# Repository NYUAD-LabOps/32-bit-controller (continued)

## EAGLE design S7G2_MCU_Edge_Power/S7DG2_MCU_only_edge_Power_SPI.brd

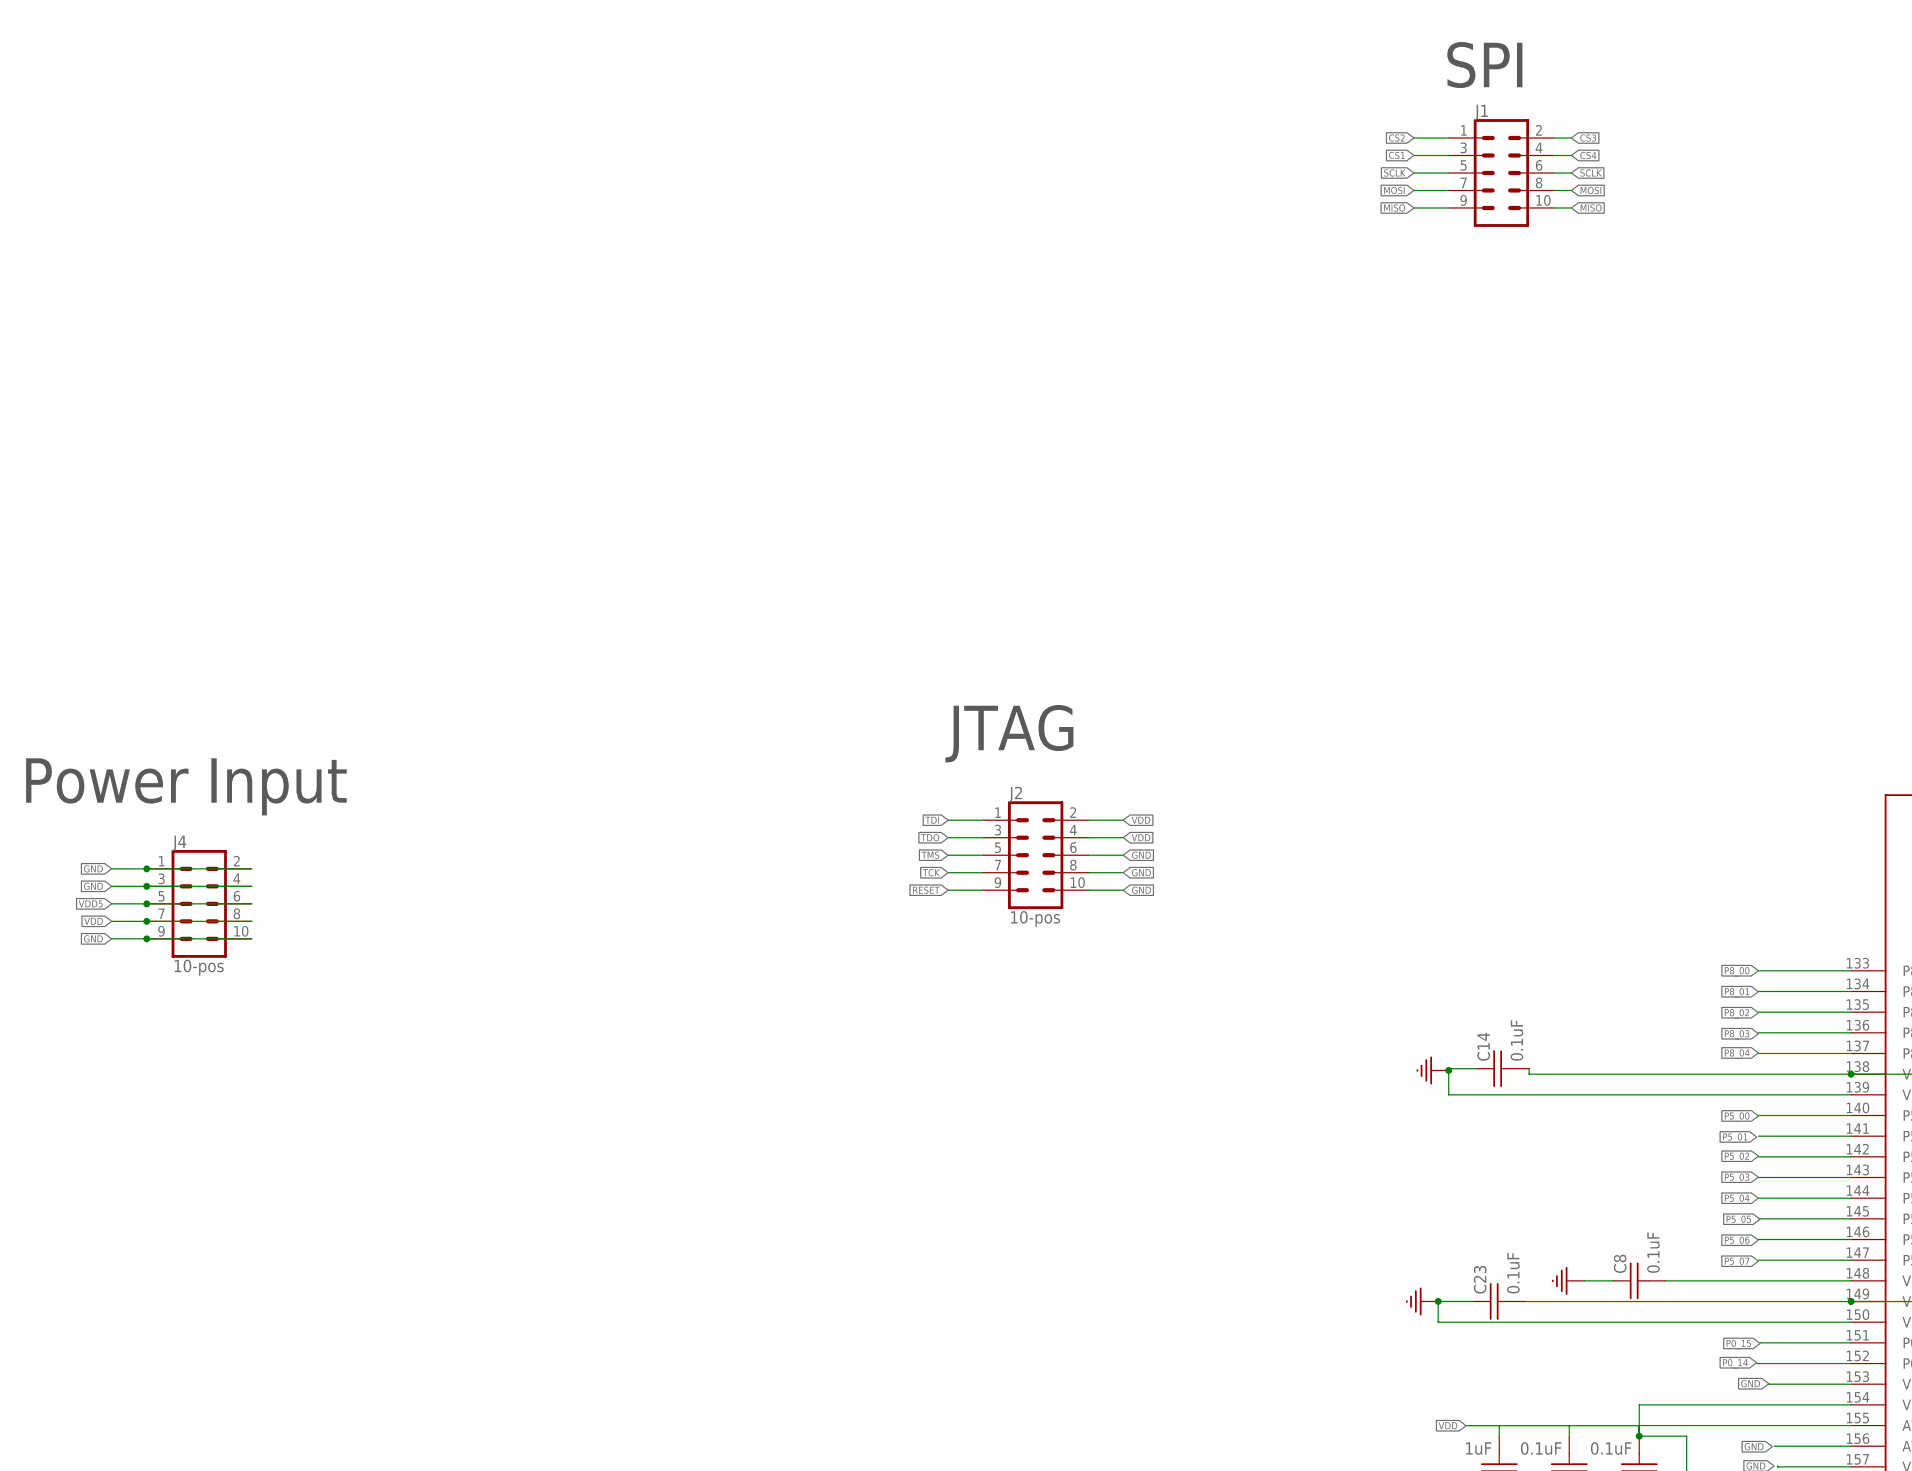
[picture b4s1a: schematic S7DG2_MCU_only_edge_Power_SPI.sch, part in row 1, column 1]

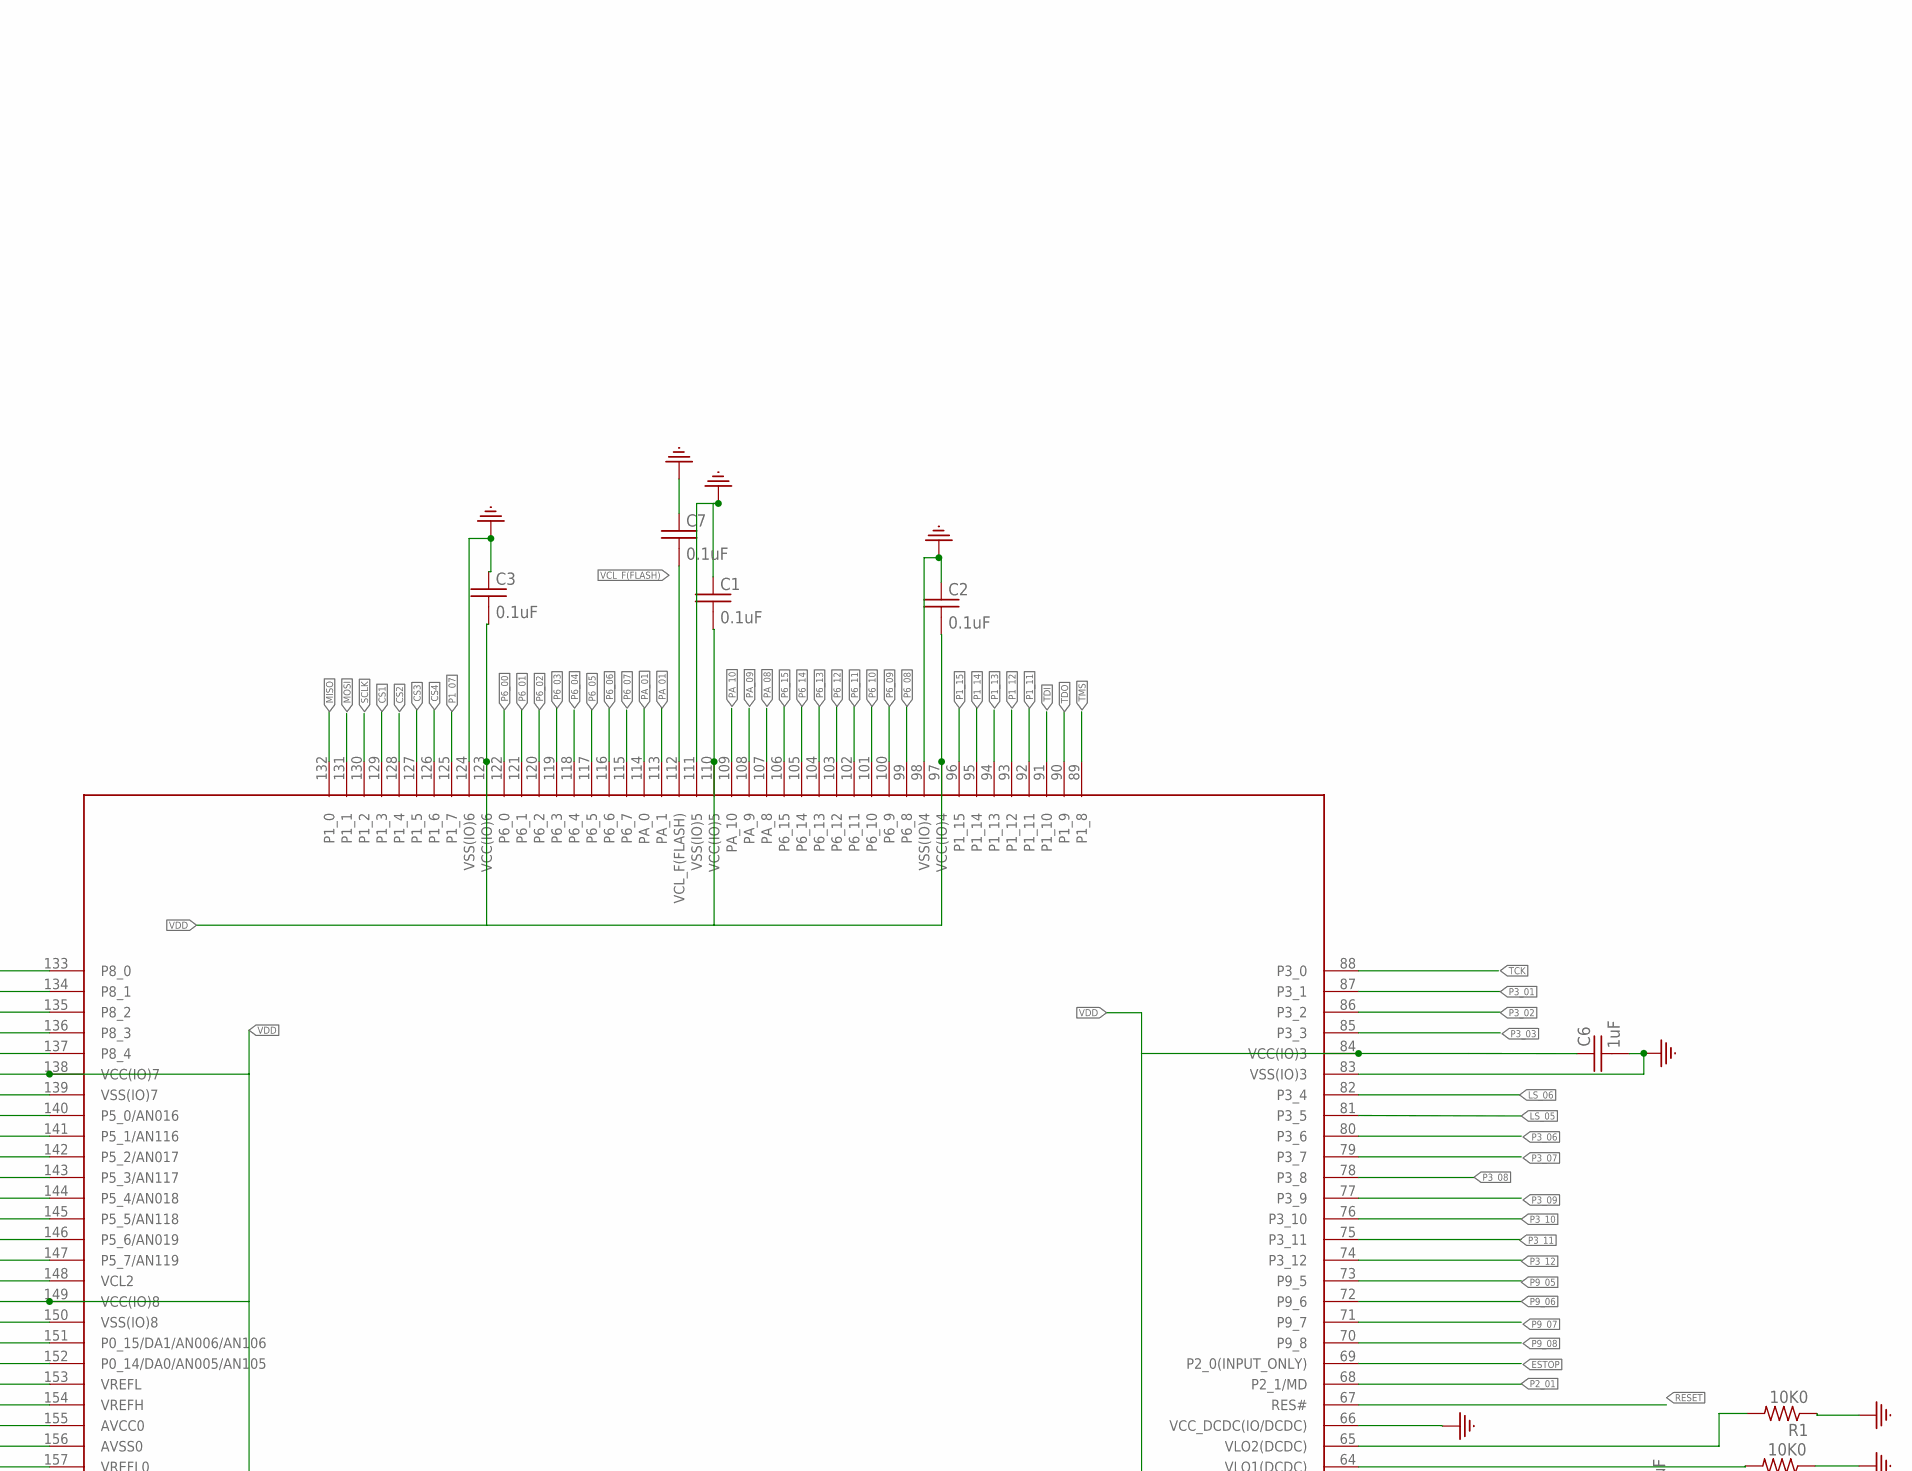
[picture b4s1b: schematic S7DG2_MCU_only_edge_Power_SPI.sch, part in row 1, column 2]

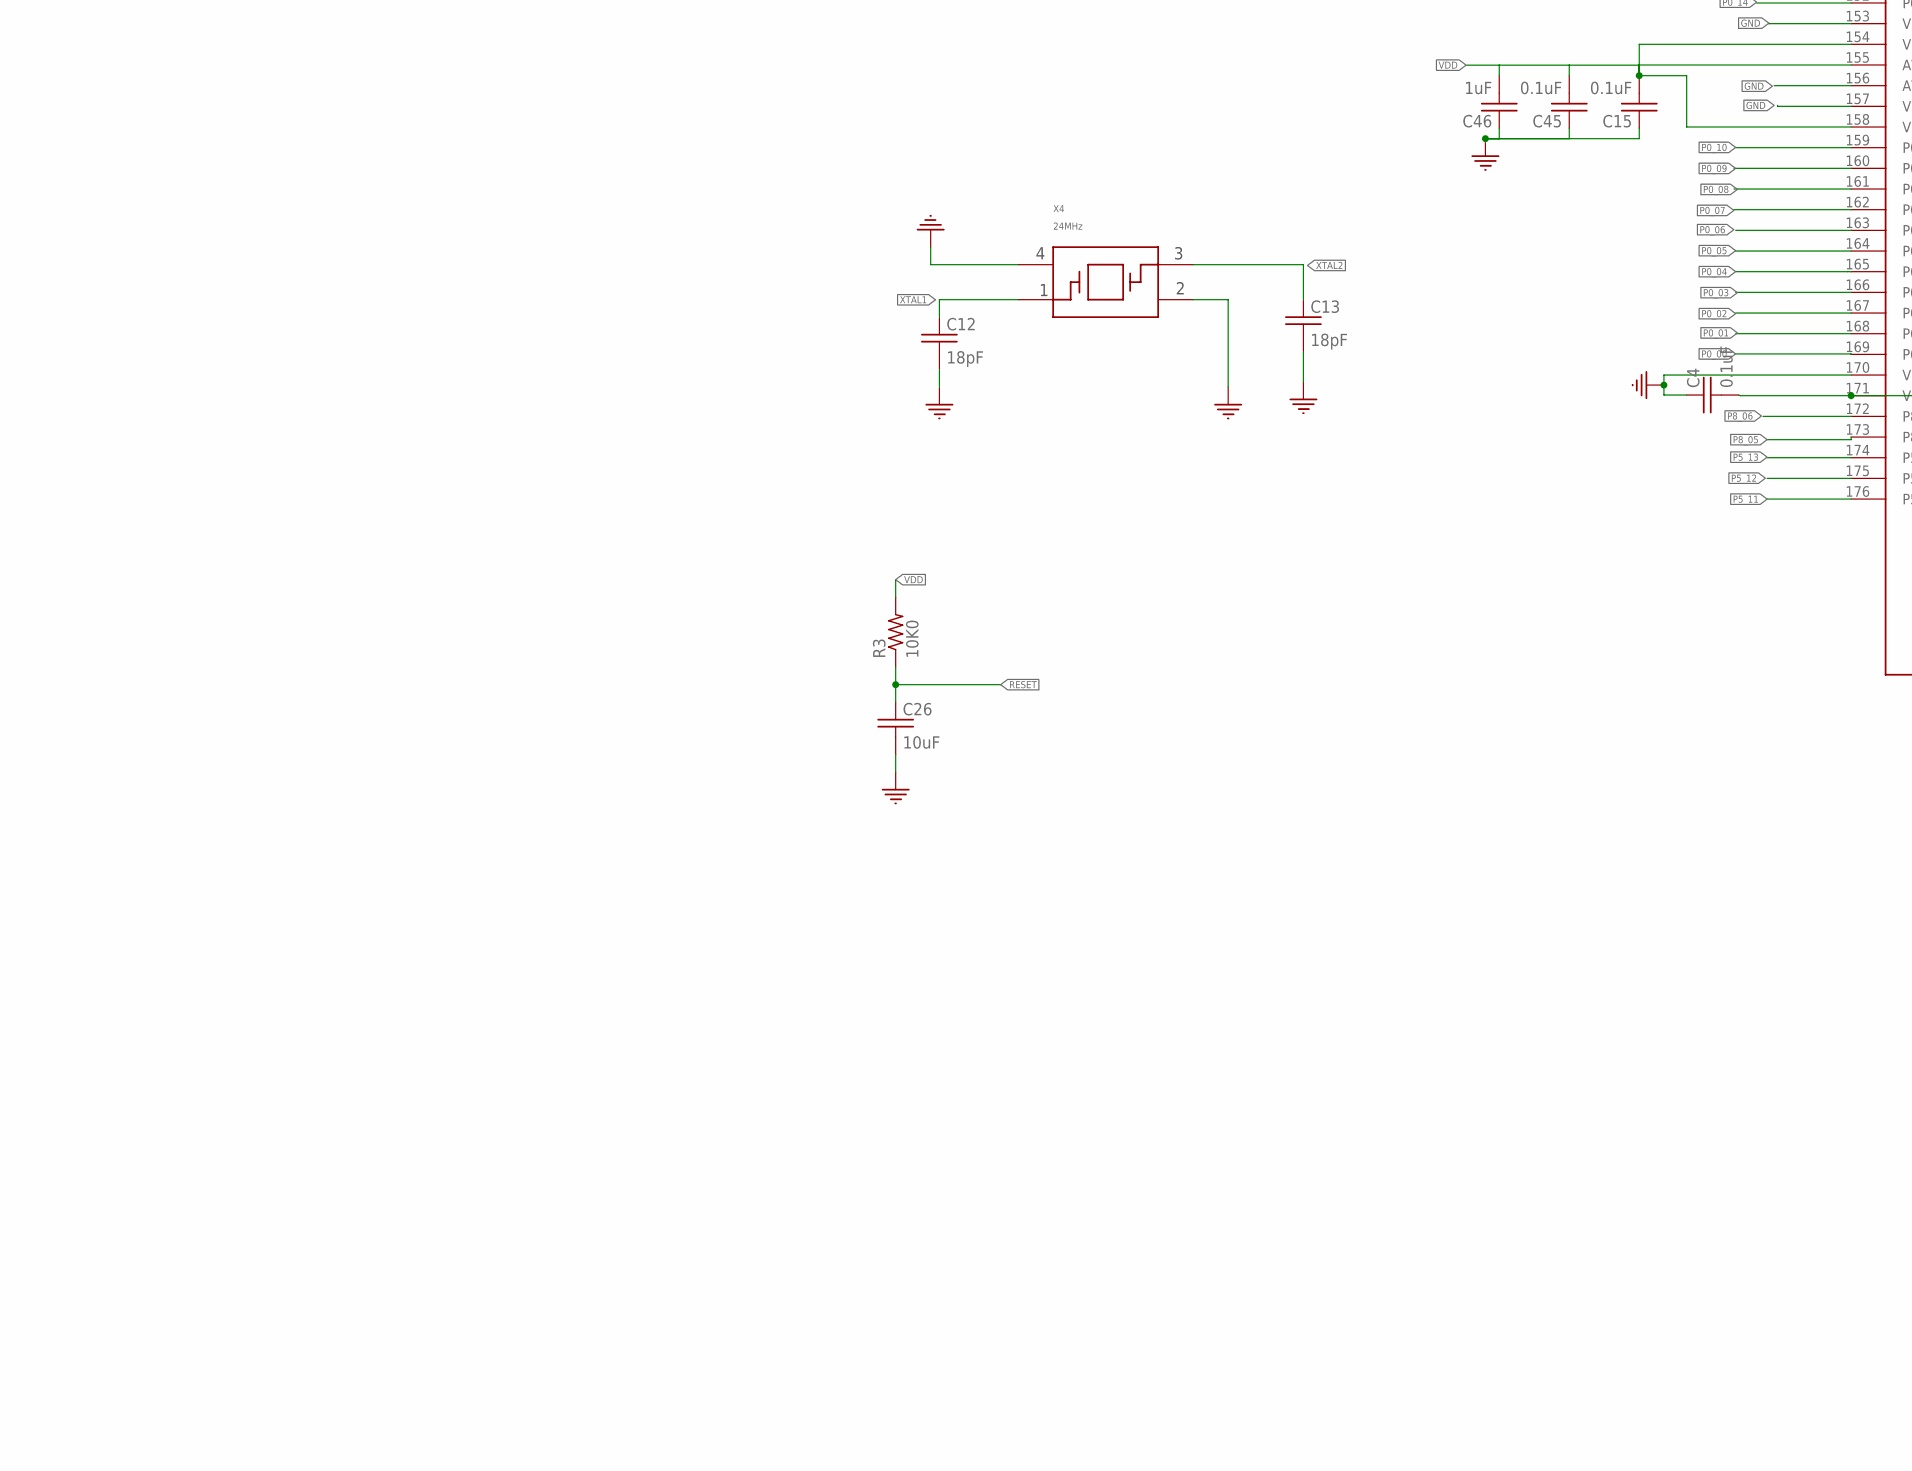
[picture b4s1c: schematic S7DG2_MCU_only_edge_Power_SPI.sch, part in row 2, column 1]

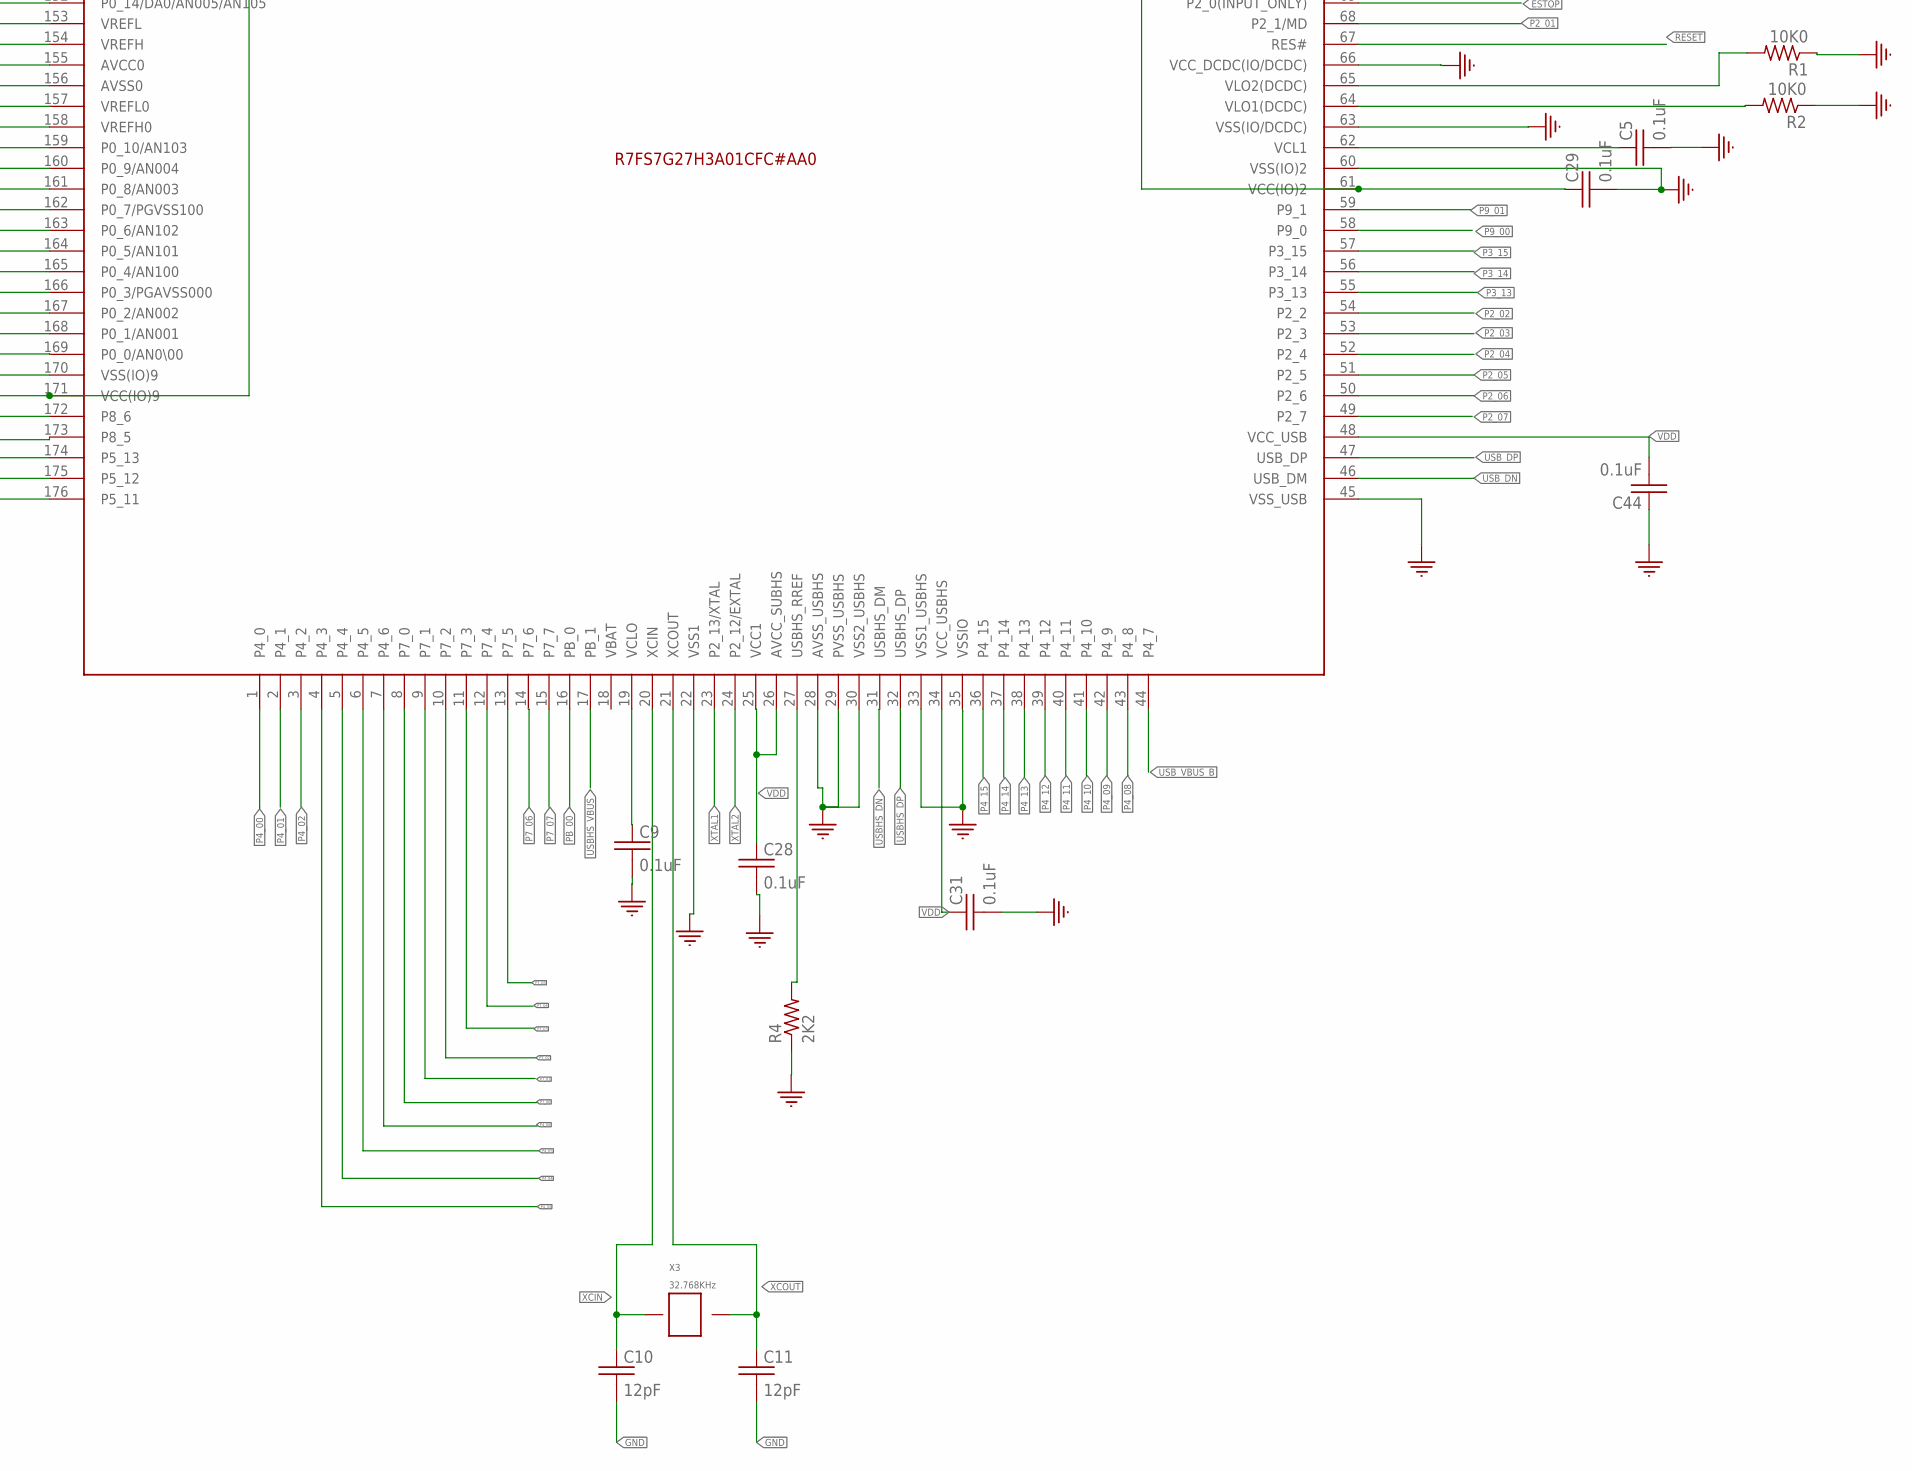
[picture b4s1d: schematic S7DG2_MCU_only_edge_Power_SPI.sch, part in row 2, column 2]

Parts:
C1, C2, C3, C4, C5, C7, C8, C9, C14, C15, C23, C28, C29, C31, C44, C45: 0.1uF; 0402
C6, C46: 1uF; 0402
C10, C11: 12pF; 0402
C12, C13: 18pF; 0402
C26: 10uF; 0402
J1: CONN_05X2PTH; 2X5
J2, J4: 10-pos; 2X5
R1, R2, R3: 10K0; 0402
R4: 2K2; 0402
U2: S7G2LQFP176; LQFP176_24X24
X3: 32.768KHz; SMD_X_2_PADS
X4: 24MHz; SMD_3225

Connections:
CS1: J1.3, U2.129 (P1_3)
CS2: J1.1, U2.128 (P1_4)
CS3: J1.2, U2.127 (P1_5)
CS4: J1.4, U2.126 (P1_6)
ESTOP: U2.69 (P2_0(INPUT_ONLY))
GND: C1.P$1 (1), C2.P$1 (1), C3.P$1 (1), C4.P$1 (1), C5.P$2 (2), C6.P$2 (2), C7.P$1 (1), C8.P$1 (1), C9.P$2 (2), C10.P$2 (2), C11.P$2 (2), C12.P$2 (2), C13.P$2 (2), C14.P$1 (1), C15.P$1 (1), C23.P$1 (1), C26.P$2 (2), C28.P$2 (2), C29.P$2 (2), C31.P$2 (2), C44.P$1 (1), C45.P$1 (1), C46.P$1 (1), J2.6, J2.8, J2.10, J4.1, J4.2, J4.3, J4.4, J4.9, J4.10, R1.P$1 (1), R2.P$1 (1), R4.P$1 (1), U2.22 (VSS1), U2.28 (AVSS_USBHS), U2.29 (PVSS_USBHS), U2.30 (VSS2_USBHS), U2.33 (VSS1_USBHS), U2.35 (VSSIO), U2.45 (VSS_USB), U2.60 (VSS(IO)2), U2.63 (VSS(IO/DCDC)), U2.66 (VCC_DCDC(IO/DCDC)), U2.83 (VSS(IO)3), U2.98 (VSS(IO)4), U2.111 (VSS(IO)5), U2.124 (VSS(IO)6), U2.139 (VSS(IO)7), U2.150 (VSS(IO)8), U2.153 (VREFL), U2.156 (AVSS0), U2.157 (VREFL0), U2.170 (VSS(IO)9), X4.2, X4.4
LS_05: U2.81 (P3_5)
LS_06: U2.82 (P3_4)
MISO: J1.9, J1.10, U2.132 (P1_0)
MOSI: J1.7, J1.8, U2.131 (P1_1)
unnamed: C8.P$2 (2), U2.148 (VCL2)
unnamed: C9.P$1 (1), U2.19 (VCLO)
unnamed: C5.P$1 (1), U2.62 (VCL1)
unnamed: R2.P$2 (2), U2.64 (VLO1(DCDC))
unnamed: R1.P$2 (2), U2.65 (VLO2(DCDC))
unnamed: R4.P$2 (2), U2.27 (USBHS_RREF)
P0_00: U2.169 (P0_0/AN0\00)
P0_01: U2.168 (P0_1/AN001)
P0_02: U2.167 (P0_2/AN002)
P0_03: U2.166 (P0_3/PGAVSS000)
P0_04: U2.165 (P0_4/AN100)
P0_05: U2.164 (P0_5/AN101)
P0_06: U2.163 (P0_6/AN102)
P0_07: U2.162 (P0_7/PGVSS100)
P0_08: U2.161 (P0_8/AN003)
P0_09: U2.160 (P0_9/AN004)
P0_10: U2.159 (P0_10/AN103)
P0_14: U2.152 (P0_14/DA0/AN005/AN105)
P0_15: U2.151 (P0_15/DA1/AN006/AN106)
P1_07: U2.125 (P1_7)
P1_11: U2.92 (P1_11)
P1_12: U2.93 (P1_12)
P1_13: U2.94 (P1_13)
P1_14: U2.95 (P1_14)
P1_15: U2.96 (P1_15)
P2_01: U2.68 (P2_1/MD)
P2_02: U2.54 (P2_2)
P2_03: U2.53 (P2_3)
P2_04: U2.52 (P2_4)
P2_05: U2.51 (P2_5)
P2_06: U2.50 (P2_6)
P2_07: U2.49 (P2_7)
P3_01: U2.87 (P3_1)
P3_02: U2.86 (P3_2)
P3_03: U2.85 (P3_3)
P3_06: U2.80 (P3_6)
P3_07: U2.79 (P3_7)
P3_08: U2.78 (P3_8)
P3_09: U2.77 (P3_9)
P3_10: U2.76 (P3_10)
P3_11: U2.75 (P3_11)
P3_12: U2.74 (P3_12)
P3_13: U2.55 (P3_13)
P3_14: U2.56 (P3_14)
P3_15: U2.57 (P3_15)
P4_00: U2.1 (P4_0)
P4_01: U2.2 (P4_1)
P4_02: U2.3 (P4_2)
P4_03: U2.4 (P4_3)
P4_04: U2.5 (P4_4)
P4_05: U2.6 (P4_5)
P4_06: U2.7 (P4_6)
P4_08: U2.43 (P4_8)
P4_09: U2.42 (P4_9)
P4_10: U2.41 (P4_10)
P4_11: U2.40 (P4_11)
P4_12: U2.39 (P4_12)
P4_13: U2.38 (P4_13)
P4_14: U2.37 (P4_14)
P4_15: U2.36 (P4_15)
P5_00: U2.140 (P5_0/AN016)
P5_01: U2.141 (P5_1/AN116)
P5_02: U2.142 (P5_2/AN017)
P5_03: U2.143 (P5_3/AN117)
P5_04: U2.144 (P5_4/AN018)
P5_05: U2.145 (P5_5/AN118)
P5_06: U2.146 (P5_6/AN019)
P5_07: U2.147 (P5_7/AN119)
P5_11: U2.176 (P5_11)
P5_12: U2.175 (P5_12)
P5_13: U2.174 (P5_13)
P6_00: U2.122 (P6_0)
P6_01: U2.121 (P6_1)
P6_02: U2.120 (P6_2)
P6_03: U2.119 (P6_3)
P6_04: U2.118 (P6_4)
P6_05: U2.117 (P6_5)
P6_06: U2.116 (P6_6)
P6_07: U2.115 (P6_7)
P6_08: U2.99 (P6_8)
P6_09: U2.100 (P6_9)
P6_10: U2.101 (P6_10)
P6_11: U2.102 (P6_11)
P6_12: U2.103 (P6_12)
P6_13: U2.104 (P6_13)
P6_14: U2.105 (P6_14)
P6_15: U2.106 (P6_15)
P7_00: U2.8 (P7_0)
P7_01: U2.9 (P7_1)
P7_02: U2.10 (P7_2)
P7_03: U2.11 (P7_3)
P7_04: U2.12 (P7_4)
P7_05: U2.13 (P7_5)
P7_06: U2.14 (P7_6)
P7_07: U2.15 (P7_7)
P8_00: U2.133 (P8_0)
P8_01: U2.134 (P8_1)
P8_02: U2.135 (P8_2)
P8_03: U2.136 (P8_3)
P8_04: U2.137 (P8_4)
P8_05: U2.173 (P8_5)
P8_06: U2.172 (P8_6)
P9_00: U2.58 (P9_0)
P9_01: U2.59 (P9_1)
P9_05: U2.73 (P9_5)
P9_06: U2.72 (P9_6)
P9_07: U2.71 (P9_7)
P9_08: U2.70 (P9_8)
PA_01: U2.113 (PA_1), U2.114 (PA_0)
PA_08: U2.107 (PA_8)
PA_09: U2.108 (PA_9)
PA_10: U2.109 (PA_10)
PB_00: U2.16 (PB_0)
RESET: C26.P$1 (1), J2.9, R3.P$1 (1), U2.67 (RES#)
SCLK: J1.5, J1.6, U2.130 (P1_2)
TCK: J2.7, U2.88 (P3_0)
TDI: J2.1, U2.91 (P1_10)
TDO: J2.3, U2.90 (P1_9)
TMS: J2.5, U2.89 (P1_8)
USBHS_DN: U2.31 (USBHS_DM)
USBHS_DP: U2.32 (USBHS_DP)
USBHS_VBUS: U2.17 (PB_1)
USB_DN: U2.46 (USB_DM)
USB_DP: U2.47 (USB_DP)
USB_VBUS_B: U2.44 (P4_7)
VCL_F(FLASH): C7.P$2 (2), U2.112 (VCL_F(FLASH))
VDD: C1.P$2 (2), C2.P$2 (2), C3.P$2 (2), C4.P$2 (2), C6.P$1 (1), C14.P$2 (2), C15.P$2 (2), C23.P$2 (2), C28.P$1 (1), C29.P$1 (1), C31.P$1 (1), C44.P$2 (2), C45.P$2 (2), C46.P$2 (2), J2.2, J2.4, J4.7, J4.8, R3.P$2 (2), U2.25 (VCC1), U2.26 (AVCC_SUBHS), U2.34 (VCC_USBHS), U2.48 (VCC_USB), U2.61 (VCC(IO)2), U2.84 (VCC(IO)3), U2.97 (VCC(IO)4), U2.110 (VCC(IO)5), U2.123 (VCC(IO)6), U2.138 (VCC(IO)7), U2.149 (VCC(IO)8), U2.154 (VREFH), U2.155 (AVCC0), U2.158 (VREFH0), U2.171 (VCC(IO)9)
VDD5: J4.5, J4.6
XCIN: C10.P$1 (1), U2.20 (XCIN), X3.P$1
XCOUT: C11.P$1 (1), U2.21 (XCOUT), X3.P$2
XTAL1: C12.P$1 (1), U2.23 (P2_13/XTAL), X4.1
XTAL2: C13.P$1 (1), U2.24 (P2_12/EXTAL), X4.3

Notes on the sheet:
Power Input
SPI
JTAG

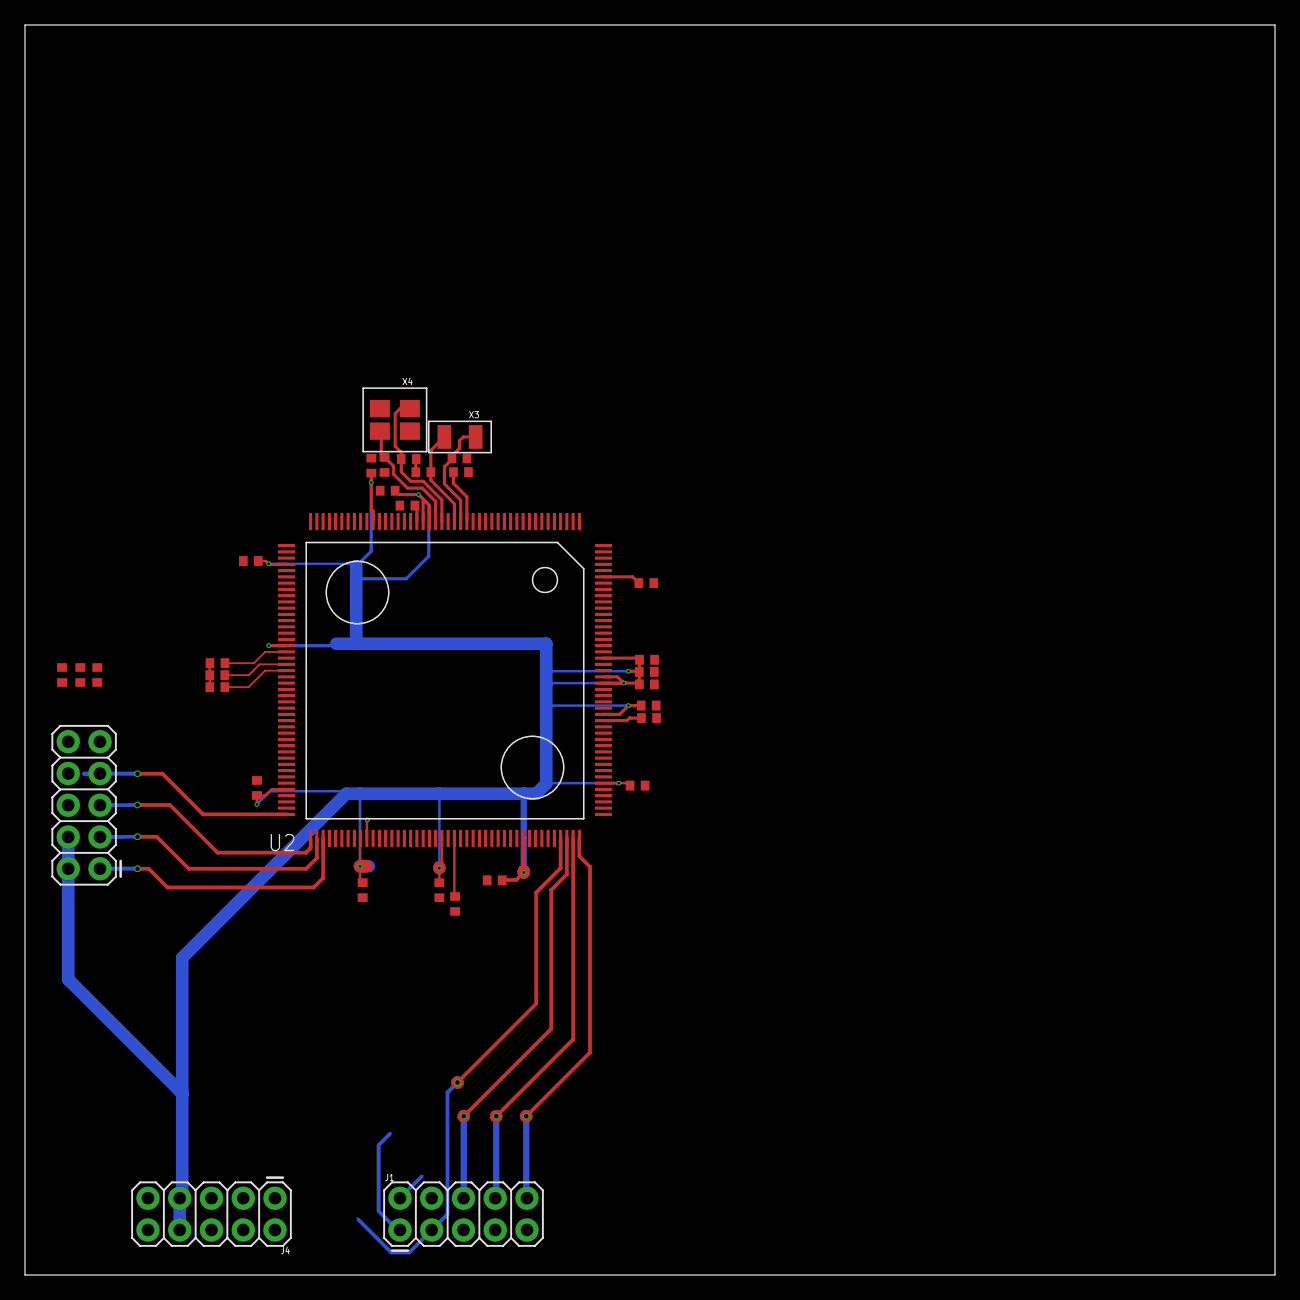
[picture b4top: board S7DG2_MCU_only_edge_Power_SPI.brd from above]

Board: 2 copper layers, 100.0 x 100.0 mm, 33 parts (0 on the bottom side), 27 nets.

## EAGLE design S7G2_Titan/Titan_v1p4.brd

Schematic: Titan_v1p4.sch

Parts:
C1, C2: 24pF; 0402
C3: 100pF; 0402
C4, C7, C9, C10, C12, C13, C15, C19, C20, C22, C24, C25, C26, C27, C29, C30, C33, C34, C35, C36, C38, C39, C40, C42, C43: 0.1uF; 0402
C5, C6, C16, C23: 10uF; 0402
C8, C14: 22uF; 0402
C11: 2.2uF; 0402
C17, C18: 18pF; 0402
C21, C28, C41: 1uF; 0402
C31: 10uF_Tant; C1210
C32, C37: 12pF; 0402
FB1: FB2_603; 0603
J1: SD_CARD
J2: 4-pos; 1X4_3.81MM_PITCH
J3, J5, J9: 10-pos; 2X5
J4, J10: 20-pos; 2_X_10_.1_INCH
J6: USB-A; USB_A_SMT
J7: USB-B-Micro; USB_MICRO-B
J8: 40-pos; HEADER_2_X_20_.1_INCH
L1: 2.2uH; 1008
LED1: Green; 0805
R1: 6K49; 0402
R2, R3, R13, R19, R20, R23, R24: 10K0; 0402
R4, R6: 1K5; 0402
R5, R7, R8: 470R0; 0402
R9, R10, R11, R12: 33R0; 0402
R14, R15: 1K0; 0402
R16: 15K0; 0402
R17, R18: 27R0; 0402
R21: 30K0; 0402
R22: 2K2; 0402
RJ1: RJ45; RJ45_TH_ELEC
U1: KSZ8081_QFN_24; QFN-24-M
U2: AP2151DWG-7; SOT-23-5
U3: S7G2LQFP176; LQFP176_24X24
U$1, U$2, U$3, U$4, U$5, U$6: FIDUCIAL_1MM
X1: 25MHz; SMD_3225
X2: 24MHz; SMD_3225
X3: 32.768KHz; SMD_X_2_PADS

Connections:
C58: C12.P$1 (1), RJ1.4 (CT1)
C60: C13.P$1 (1), RJ1.5 (CT2)
CRS_DV: R12.P$2 (2), U1.15 (CRS_DV/PHYAD[1:0])
D+: J7.P$3 (D+), R18.P$2 (2)
D-: J7.P$2 (D-), R17.P$2 (2)
ETH: U1.16 (REF_CLK), U3.9 (P7_1)
ETH_CRS_DV: R12.P$1 (1), U3.13 (P7_5)
ETH_IRQ14: R2.P$1 (1), U1.18 (INTRP), U3.159 (P0_10/AN103)
ETH_MDC: R4.P$1 (1), U1.11 (MDC), U3.4 (P4_3)
ETH_MDIO: R6.P$1 (1), U1.10 (MDIO), U3.5 (P4_4)
ETH_RESET: C6.P$1 (1), R3.P$1 (1), U1.24 (!RST), U3.172 (P8_6)
ETH_RXD0: R10.P$1 (1), U3.10 (P7_2)
ETH_RXD1: R9.P$1 (1), U3.11 (P7_3)
ETH_RX_ER: R11.P$1 (1), U3.12 (P7_4)
ETH_TXD0: U1.20 (TXD0), U3.8 (P7_0)
ETH_TXD1: U1.21 (TXD1), U3.7 (P4_6)
ETH_TXD_EN: U1.19 (TXEN), U3.6 (P4_5)
GND: C1.P$2 (2), C2.P$2 (2), C3.P$2 (2), C4.P$2 (2), C5.P$2 (2), C6.P$2 (2), C7.P$2 (2), C8.P$2 (2), C9.P$2 (2), C10.P$2 (2), C11.P$2 (2), C12.P$2 (2), C13.P$2 (2), C14.P$2 (2), C15.P$2 (2), C16.P$2 (2), C17.P$2 (2), C18.P$2 (2), C19.P$1 (1), C20.P$1 (1), C21.P$1 (1), C22.P$1 (1), C23.P$2 (2), C24.P$1 (1), C25.P$1 (1), C26.P$2 (2), C27.P$1 (1), C28.P$2 (2), C29.P$2 (2), C30.P$1 (1), C31.2, C32.P$2 (2), C33.P$2 (2), C34.P$1 (1), C35.P$1 (1), C36.P$2 (2), C37.P$2 (2), C38.P$1 (1), C39.P$2 (2), C40.P$2 (2), C41.P$2 (2), C42.P$2 (2), C43.P$1 (1), J1.6 (SUPPLY_VOLTAGE_GROUND), J2.P$1, J3.6, J3.8, J3.10, J6.GND, J7.P$5 (GND), J8.P$1, J9.2, J9.4, J9.6, J9.8, J9.10, LED1.2 (C), R1.P$1 (1), R21.P$1 (1), R22.P$1 (1), R23.P$1 (1), R24.P$1 (1), RJ1.8, RJ1.10 (GLO), U1.22 (GND), U1.25, U2.2 (GND), U3.22 (VSS1), U3.28 (AVSS_USBHS), U3.29 (PVSS_USBHS), U3.30 (VSS2_USBHS), U3.33 (VSS1_USBHS), U3.35 (VSSIO), U3.45 (VSS_USB), U3.60 (VSS(IO)2), U3.63 (VSS(IO/DCDC)), U3.66 (VCC_DCDC(IO/DCDC)), U3.83 (VSS(IO)3), U3.98 (VSS(IO)4), U3.111 (VSS(IO)5), U3.124 (VSS(IO)6), U3.139 (VSS(IO)7), U3.150 (VSS(IO)8), U3.153 (VREFL), U3.156 (AVSS0), U3.157 (VREFL0), U3.170 (VSS(IO)9), X1.2, X1.4, X2.2, X2.4
GNDE: J1.S1 (SHIELD), J1.S2 (SHIELD), J1.S3 (SHIELD), J1.S4 (SHIELD), J2.P$4, J6.SHLD1 (SHIELD_1), J6.SHLD2 (SHIELD_2), J7.P$6 (SHIELD1), J7.P$7 (SHIELD2), J7.P$8 (SHIELD3), J7.P$9 (SHIELD4), RJ1.13 (GNDE0), RJ1.14 (GNDE1)
ID: J7.P$4 (ID)
IIC_1_SCL: J8.P$5, R14.P$2 (2), U3.132 (P1_0)
IIC_1_SDA: J8.P$6, R15.P$2 (2), U3.131 (P1_1)
INT_MI_01: J8.P$39, U3.87 (P3_1)
INT_MI_02: J8.P$40, U3.86 (P3_2)
INT_MI_03: J8.P$9, U3.128 (P1_4)
INT_MI_04: J8.P$10, U3.127 (P1_5)
LED1/SPEED: RJ1.11 (YLO), U1.23 (LED0/ANEN_SPEED)
unnamed: C24.P$2 (2), U3.148 (VCL2)
unnamed: LED1.1 (A), R5.P$1 (1)
unnamed: C33.P$1 (1), U3.19 (VCLO)
unnamed: C42.P$1 (1), U3.62 (VCL1)
unnamed: R23.P$2 (2), U3.64 (VLO1(DCDC))
unnamed: R24.P$2 (2), U3.65 (VLO2(DCDC))
unnamed: R22.P$2 (2), U3.27 (USBHS_RREF)
NC: RJ1.7
P0_00: J4.P$2, U3.169 (P0_0/AN0\00)
P0_01: J4.P$1, U3.168 (P0_1/AN001)
P0_02: J5.1, U3.167 (P0_2/AN002)
P0_03: J5.3, U3.166 (P0_3/PGAVSS000)
P0_04: J5.5, U3.165 (P0_4/AN100)
P0_05: J5.7, U3.164 (P0_5/AN101)
P0_06: J5.9, U3.163 (P0_6/AN102)
P0_07: J5.10, U3.162 (P0_7/PGVSS100)
P0_08: J5.8, U3.161 (P0_8/AN003)
P0_09: J5.6, U3.160 (P0_9/AN004)
P0_14: J5.4, U3.152 (P0_14/DA0/AN005/AN105)
P0_15: J5.2, U3.151 (P0_15/DA1/AN006/AN106)
P1_02: J8.P$7, U3.130 (P1_2)
P1_03: J8.P$8, U3.129 (P1_3)
P1_06: J8.P$11, U3.126 (P1_6)
P1_07: J8.P$12, U3.125 (P1_7)
P1_11: J8.P$38, U3.92 (P1_11)
P1_12: J8.P$37, U3.93 (P1_12)
P1_13: J8.P$36, U3.94 (P1_13)
P1_14: J8.P$35, U3.95 (P1_14)
P1_15: J8.P$34, U3.96 (P1_15)
P2_00: J10.P$13, U3.69 (P2_0(INPUT_ONLY))
P2_01: J10.P$14, U3.68 (P2_1/MD)
P2_02: J10.P$19, U3.54 (P2_2)
P2_03: J9.1, U3.53 (P2_3)
P2_04: J9.3, U3.52 (P2_4)
P2_05: J9.5, U3.51 (P2_5)
P2_06: J9.7, U3.50 (P2_6)
P2_07: J9.9, U3.49 (P2_7)
P3_03: J10.P$2, U3.85 (P3_3)
P3_04: J10.P$4, U3.82 (P3_4)
P3_05: J10.P$6, U3.81 (P3_5)
P3_06: J10.P$1, U3.80 (P3_6)
P3_07: J10.P$3, U3.79 (P3_7)
P3_09: J10.P$5, U3.77 (P3_9)
P3_10: J10.P$7, U3.76 (P3_10)
P3_11: J10.P$8, U3.75 (P3_11)
P3_12: J10.P$9, U3.74 (P3_12)
P3_13: J10.P$20, U3.55 (P3_13)
P3_14: J10.P$17, U3.56 (P3_14)
P3_15: J10.P$18, U3.57 (P3_15)
P4_00: J4.P$7, U3.1 (P4_0)
P4_01: J4.P$8, U3.2 (P4_1)
P4_02: J4.P$9, U3.3 (P4_2)
P4_08: J4.P$20, U3.43 (P4_8)
P4_09: J4.P$19, U3.42 (P4_9)
P4_10: J4.P$18, U3.41 (P4_10)
P4_11: J4.P$17, U3.40 (P4_11)
P4_12: J4.P$16, U3.39 (P4_12)
P4_13: J4.P$15, U3.38 (P4_13)
P4_14: J4.P$14, U3.37 (P4_14)
P4_15: J4.P$13, U3.36 (P4_15)
P5_11: J4.P$6, U3.176 (P5_11)
P5_12: J4.P$5, U3.175 (P5_12)
P5_13: J4.P$4, U3.174 (P5_13)
P6_00: J8.P$13, U3.122 (P6_0)
P6_01: J8.P$14, U3.121 (P6_1)
P6_02: J8.P$15, U3.120 (P6_2)
P6_03: J8.P$16, U3.119 (P6_3)
P6_04: J8.P$17, U3.118 (P6_4)
P6_05: J8.P$18, U3.117 (P6_5)
P6_06: J8.P$19, U3.116 (P6_6)
P6_07: J8.P$20, U3.115 (P6_7)
P6_08: J8.P$33, U3.99 (P6_8)
P6_09: J8.P$32, U3.100 (P6_9)
P6_10: J8.P$31, U3.101 (P6_10)
P6_11: J8.P$30, U3.102 (P6_11)
P6_12: J8.P$29, U3.103 (P6_12)
P6_13: J8.P$28, U3.104 (P6_13)
P6_14: J8.P$27, U3.105 (P6_14)
P6_15: J8.P$26, U3.106 (P6_15)
P7_06: J4.P$10, U3.14 (P7_6)
P7_07: J4.P$11, U3.15 (P7_7)
P8_00: J8.P$4, U3.133 (P8_0)
P8_01: J8.P$3, U3.134 (P8_1)
P8_02: J8.P$2, U3.135 (P8_2)
P8_03: U3.136 (P8_3)
P8_04: U3.137 (P8_4)
P8_05: J4.P$3, U3.173 (P8_5)
P9_00: J10.P$16, U3.58 (P9_0)
P9_01: J10.P$15, U3.59 (P9_1)
P9_05: J10.P$10, U3.73 (P9_5)
P9_06: J10.P$11, U3.72 (P9_6)
P9_07: J10.P$12, U3.71 (P9_7)
P9_08: U3.70 (P9_8)
PA_00: J8.P$21, U3.114 (PA_0)
PA_01: J8.P$22, U3.113 (PA_1)
PA_08: J8.P$25, U3.107 (PA_8)
PA_09: J8.P$24, U3.108 (PA_9)
PA_10: J8.P$23, U3.109 (PA_10)
PB_00: J4.P$12, U3.16 (PB_0)
R51: R7.P$1 (1), RJ1.12 (YHI)
R52: R8.P$1 (1), RJ1.9 (GHI)
RESET: C16.P$1 (1), J3.9, R13.P$1 (1), U3.67 (RES#)
REXT: C3.P$1 (1), R1.P$2 (2), U1.9 (REXT)
RXD0: R10.P$2 (2), U1.13 (RXD0)
RXD1: R9.P$2 (2), U1.12 (RXD1)
RXER: R11.P$2 (2), U1.17 (RXER)
RXM: RJ1.6 (RD-), U1.3 (RXM)
RXP: RJ1.3 (RD+), U1.4 (RXP)
SD1_CD: J1.10 (CD_SWITCH2), U3.146 (P5_6/AN019)
SD1_CLK: J1.5 (CLOCK), U3.140 (P5_0/AN016)
SD1_CMD: J1.3 (COMMAND/RESPONSE), U3.141 (P5_1/AN116)
SD1_DAT0: J1.7 (DATA_LINE[BIT_0]), U3.142 (P5_2/AN017)
SD1_DAT1: J1.8 (DATA_LINE[BIT_1]), U3.143 (P5_3/AN117)
SD1_DAT2: J1.1 (DATA_LINE[BIT_2]), U3.144 (P5_4/AN018)
SD1_DAT3: J1.2 (CARD_DETECT/DATA_LINE[BIT_3]), U3.145 (P5_5/AN118)
SD1_WP: J1.9 (CD_SWITCH1), U3.147 (P5_7/AN119)
TCK: J3.7, U3.88 (P3_0)
TDI: J3.1, U3.91 (P1_10)
TDO: J3.3, U3.90 (P1_9)
TMS: J3.5, U3.89 (P1_8)
TXM: RJ1.2 (TD-), U1.5 (TXM)
TXP: RJ1.1 (TD+), U1.6 (TXP)
USBHS_FAULT: R19.P$1 (1), U2.3 (FLG), U3.78 (P3_8)
USBHS_N: J6.D-, U3.31 (USBHS_DM)
USBHS_P: J6.D+, U3.32 (USBHS_DP)
USBHS_VBUS: C29.P$1 (1), C31.1, J6.VBUS, U2.5 (OUT), U3.17 (PB_1)
USBHS_VBUSEN: R20.P$1 (1), U2.1 (EN)
USB_N: R17.P$1 (1), U3.46 (USB_DM)
USB_P: R18.P$1 (1), U3.47 (USB_DP)
USB_VBUS_B: R16.P$1 (1), U3.44 (P4_7)
VBUS: C28.P$1 (1), J7.P$1 (VBUS), R16.P$2 (2), R21.P$2 (2)
VCL_F(FLASH): C34.P$2 (2), U3.112 (VCL_F(FLASH))
VDD: C4.P$1 (1), C5.P$1 (1), C7.P$1 (1), C14.P$1 (1), C15.P$1 (1), C19.P$2 (2), C20.P$2 (2), C21.P$2 (2), C22.P$2 (2), C25.P$2 (2), C27.P$2 (2), C30.P$2 (2), C35.P$2 (2), C36.P$1 (1), C38.P$2 (2), C39.P$1 (1), C40.P$1 (1), C41.P$1 (1), C43.P$2 (2), FB1.1, J1.4 (SUPPLY_VOLTAGE), J3.2, J3.4, L1.2, R2.P$2 (2), R3.P$2 (2), R4.P$2 (2), R5.P$2 (2), R6.P$2 (2), R7.P$2 (2), R8.P$2 (2), R13.P$2 (2), R14.P$1 (1), R15.P$1 (1), U1.14 (VDDIO), U3.25 (VCC1), U3.26 (AVCC_SUBHS), U3.34 (VCC_USBHS), U3.48 (VCC_USB), U3.61 (VCC(IO)2), U3.84 (VCC(IO)3), U3.97 (VCC(IO)4), U3.110 (VCC(IO)5), U3.123 (VCC(IO)6), U3.138 (VCC(IO)7), U3.149 (VCC(IO)8), U3.154 (VREFH), U3.155 (AVCC0), U3.158 (VREFH0), U3.171 (VCC(IO)9)
VDD5: C23.P$1 (1), C26.P$1 (1), J2.P$3, R19.P$2 (2), R20.P$2 (2), U2.4 (VIN)
VDDIN: J2.P$2, L1.1
VDD_1.2: C10.P$1 (1), C11.P$1 (1), U1.1 (VDD_1.2)
VDD_ENET1: C8.P$1 (1), C9.P$1 (1), FB1.2, U1.2 (VDDA_3.3)
XCIN: C32.P$1 (1), U3.20 (XCIN), X3.P$1
XCOUT: C37.P$1 (1), U3.21 (XCOUT), X3.P$2
XII: C1.P$1 (1), U1.8 (XI), X1.1
XOO: C2.P$1 (1), U1.7 (XO), X1.3
XTAL1: C17.P$1 (1), U3.23 (P2_13/XTAL), X2.1
XTAL2: C18.P$1 (1), U3.24 (P2_12/EXTAL), X2.3

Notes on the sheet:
Power Input
JTAG
